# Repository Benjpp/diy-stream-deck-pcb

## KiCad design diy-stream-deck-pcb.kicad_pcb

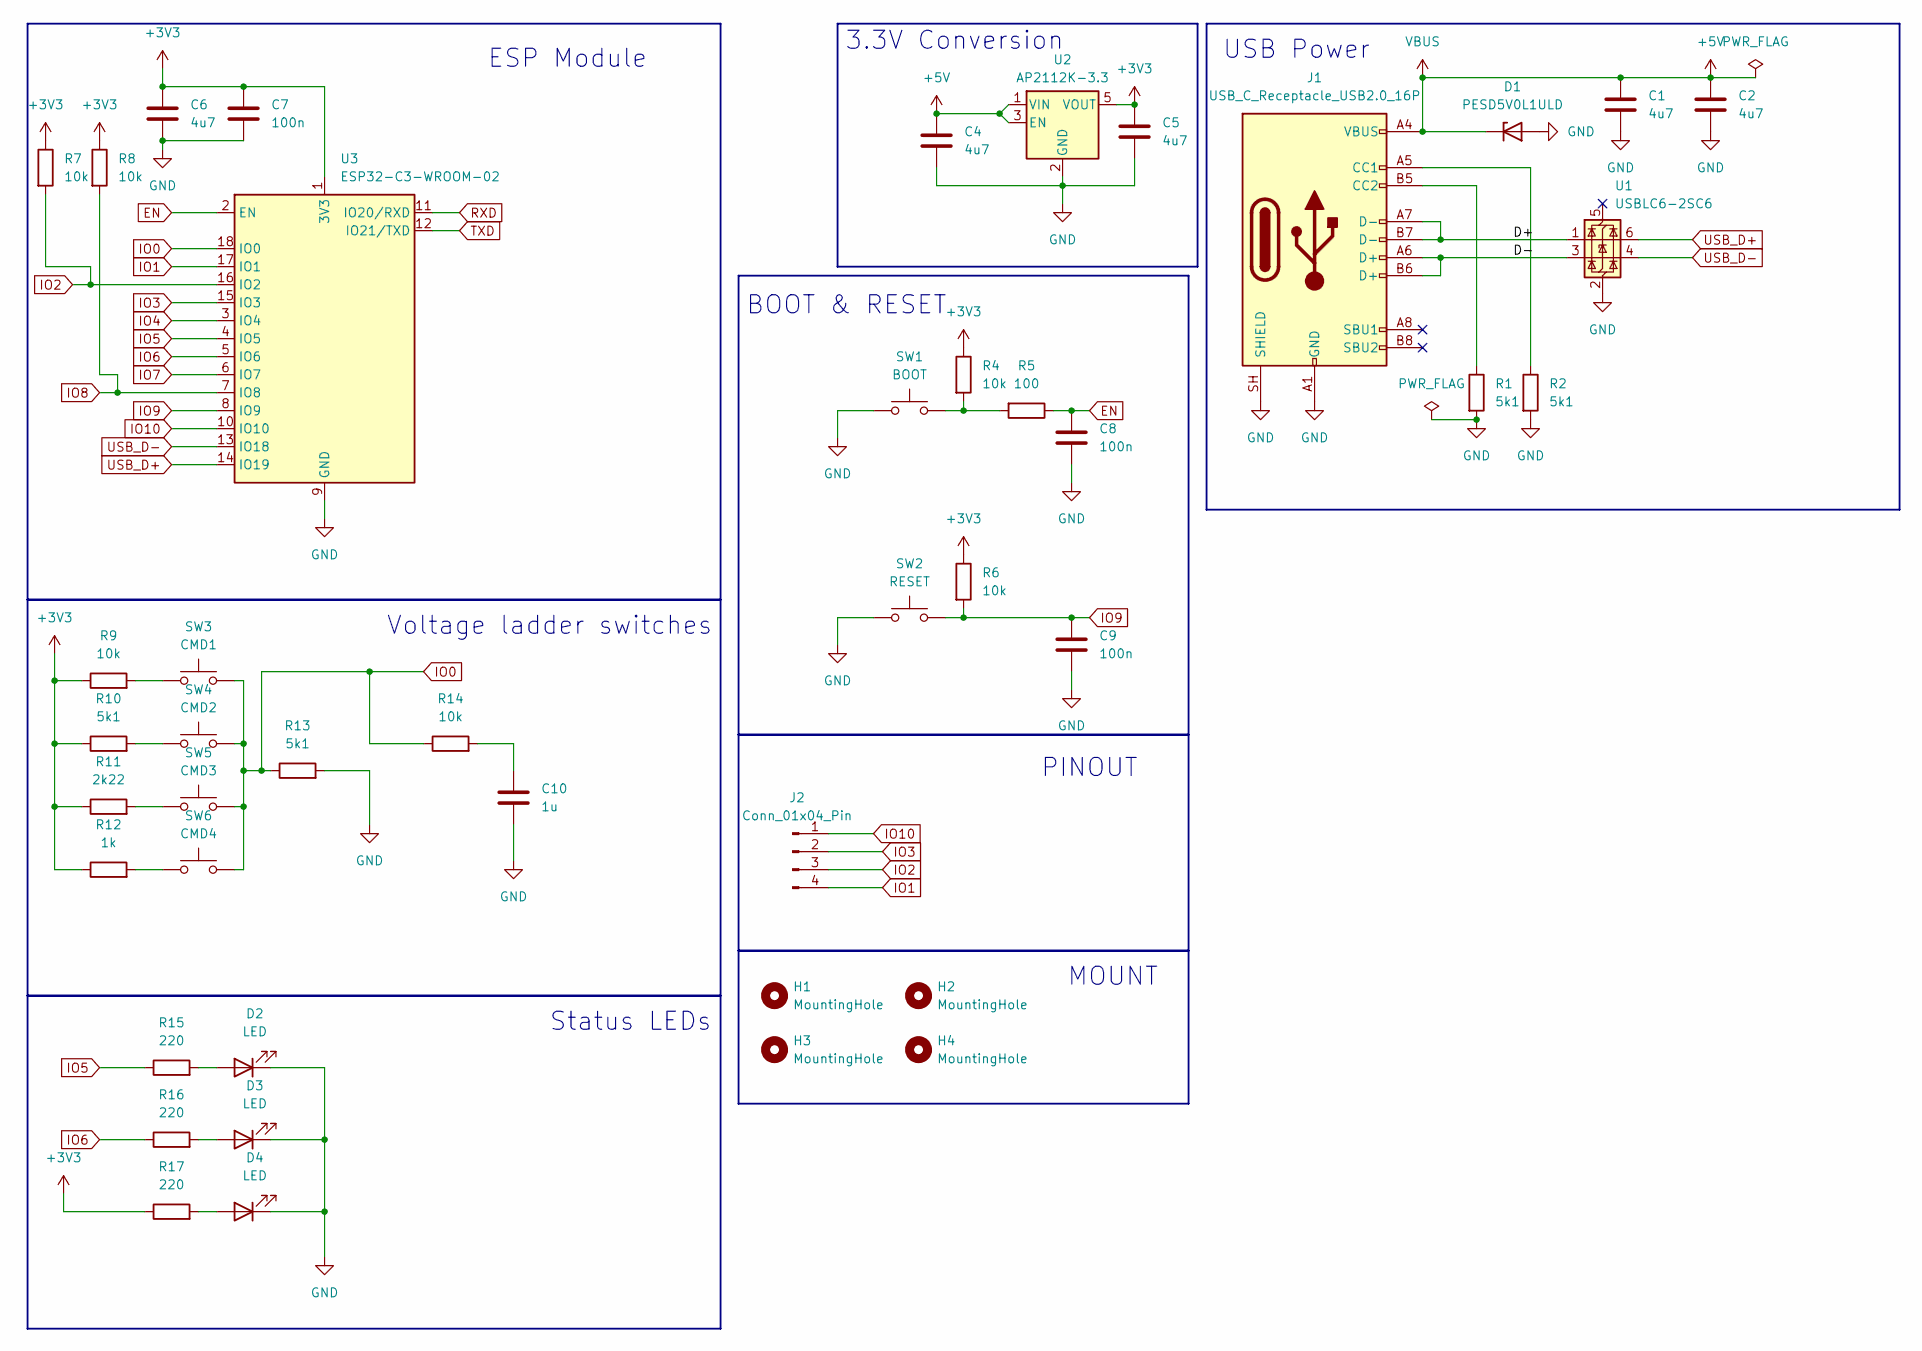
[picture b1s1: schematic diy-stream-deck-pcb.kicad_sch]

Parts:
C1, C2, C4, C5, C6: 4u7; C_0805_2012Metric
C7, C8, C9: 100n; C_0805_2012Metric
C10: 1u; C_Rect_L7.2mm_W5.0mm_P5.00mm
D1: PESD5V0L1ULD; D_SOD-882D
D2, D3, D4: LED; LED_D5.0mm
H1, H2, H3, H4: MountingHole; MountingHole_2.2mm_M2
J1: USB_C_Receptacle_USB2.0_16P; USB_C_Receptacle_G-Switch_GT-USB-7025
J2: Conn_01x04_Pin; PinHeader_1x04_P2.54mm_Vertical
R1, R2: 5k1; R_01005_0402Metric
R4, R6, R7, R8: 10k; R_0805_2012Metric
R5: 100; R_0805_2012Metric
R9, R14: 10k; R_Axial_DIN0207_L6.3mm_D2.5mm_P10.16mm_Horizontal
R10, R13: 5k1; R_Axial_DIN0207_L6.3mm_D2.5mm_P10.16mm_Horizontal
R11: 2k22; R_Axial_DIN0207_L6.3mm_D2.5mm_P10.16mm_Horizontal
R12: 1k; R_Axial_DIN0207_L6.3mm_D2.5mm_P10.16mm_Horizontal
R15, R16, R17: 220; R_Axial_DIN0207_L6.3mm_D2.5mm_P10.16mm_Horizontal
SW1: BOOT; SW_SPST_B3U-1000P
SW2: RESET; SW_SPST_B3U-1000P
SW3: CMD1; SW_SPST_B3U-1000P
SW4: CMD2; SW_SPST_B3U-1000P
SW5: CMD3; SW_SPST_B3U-1000P
SW6: CMD4; SW_SPST_B3U-1000P
U1: USBLC6-2SC6; SOT-23-6
U2: AP2112K-3.3; SOT-23-5
U3: ESP32-C3-WROOM-02

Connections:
+3V3: C5.1, C6.1, C7.1, R4.1, R6.1, R7.1, R8.1, R9.1, R10.1, R11.1, R12.1, R17.1, U2.5 (VOUT), U3.1 (3V3)
+5V: C1.1, C2.1, C4.1, D1.1 (K), J1.A4 (VBUS), J1.A9 (VBUS), J1.B4 (VBUS), J1.B9 (VBUS), U2.1 (VIN), U2.3 (EN)
/D+: J1.A7 (D-), J1.B7 (D-), U1.1 (I/O1)
/D-: J1.A6 (D+), J1.B6 (D+), U1.3 (I/O2)
EN: C8.1, R5.1, U3.2 (EN)
GND: C1.2, C2.2, C4.2, C5.2, C6.2, C7.2, C8.2, C9.2, C10.2, D1.2 (A), D2.1 (K), D3.1 (K), D4.1 (K), J1.A1 (GND), J1.A12 (GND), J1.B1 (GND), J1.B12 (GND), J1.SH (SHIELD), R1.2, R2.2, R13.2, SW1.1, SW2.1, U1.2 (GND), U2.2 (GND), U3.9 (GND), U3.19 (GND)
IO0: R13.1, R14.1, SW3.2, SW4.2, SW5.2, SW6.2, U3.18 (IO0)
IO1: J2.4, U3.17 (IO1)
IO2: J2.3, R7.2, U3.16 (IO2)
IO3: J2.2, U3.15 (IO3)
IO4: U3.3 (IO4)
IO5: R15.1, U3.4 (IO5)
IO6: R16.1, U3.5 (IO6)
IO7: U3.6 (IO7)
IO8: R8.2, U3.7 (IO8)
IO9: C9.1, R6.2, SW2.2, U3.8 (IO9)
IO10: J2.1, U3.10 (IO10)
unnamed: C10.1, R14.2
unnamed: D2.2 (A), R15.2
unnamed: D3.2 (A), R16.2
unnamed: D4.2 (A), R17.2
unnamed: J1.A5 (CC1), R2.1
unnamed: J1.B5 (CC2), R1.1
unnamed: R4.2, R5.2, SW1.2
unnamed: R9.2, SW3.1
unnamed: R10.2, SW4.1
unnamed: R11.2, SW5.1
unnamed: R12.2, SW6.1
RXD: U3.11 (IO20/RXD)
TXD: U3.12 (IO21/TXD)
USB_D+: U1.6 (I/O1), U3.14 (IO19)
USB_D-: U1.4 (I/O2), U3.13 (IO18)

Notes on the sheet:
BOOT & RESET
MOUNT
ESP Module
Status LEDs
3.3V Conversion
Voltage ladder switches
USB Power
PINOUT

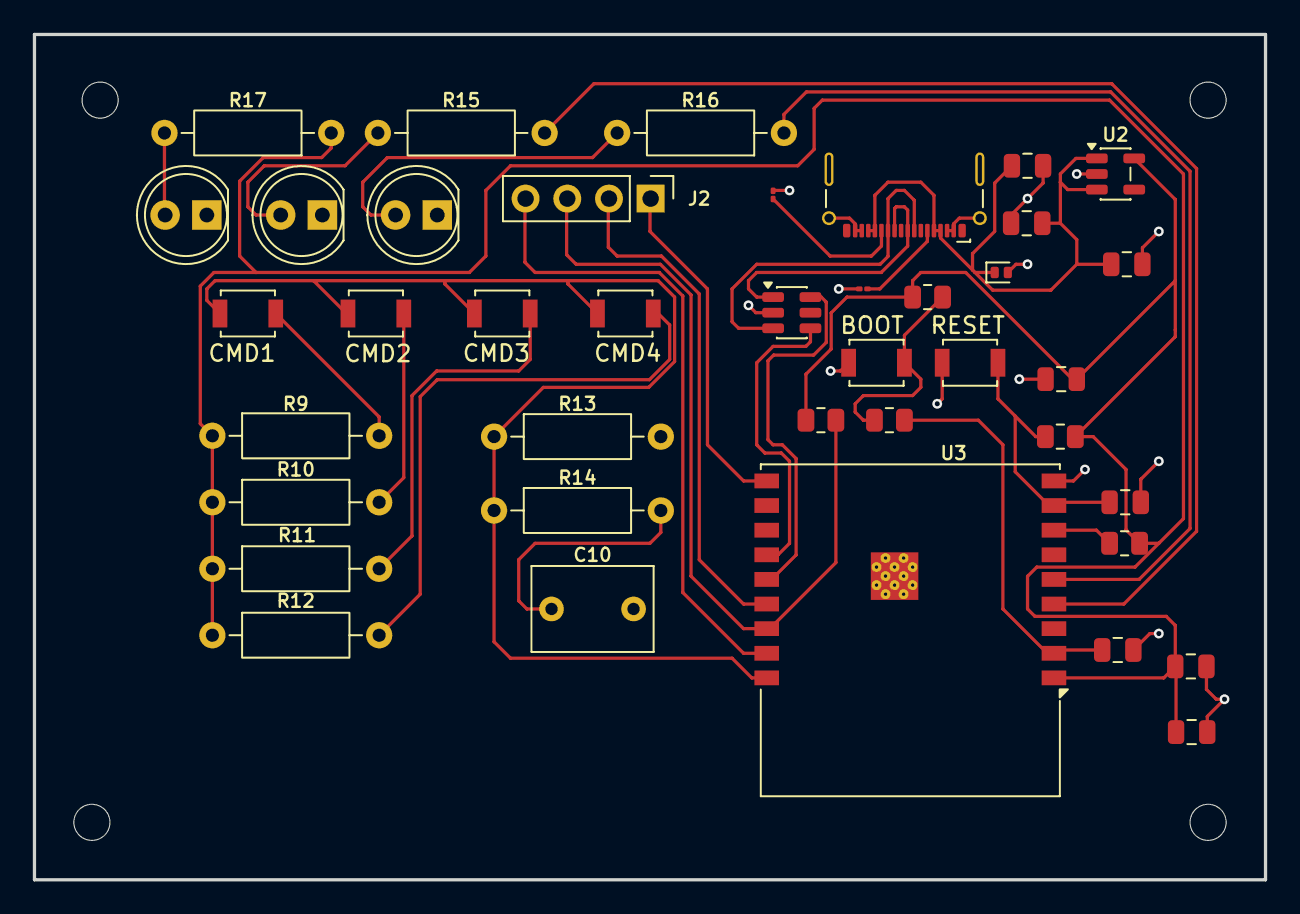
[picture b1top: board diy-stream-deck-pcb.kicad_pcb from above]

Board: 2 copper layers, 75.0 x 51.5 mm, 44 parts (0 on the bottom side), 28 nets.

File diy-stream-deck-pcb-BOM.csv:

"Id";"Identificador";"Huella";"Cantidad";"Identificación";"Suministrador y ref";
1;"C1, C2, C4, C5, C6";"C_0805_2012Metric";5;"4u7";;;
2;"C7, C8, C9";"C_0805_2012Metric";3;"100n";;;
3;"C10";"C_Rect_L7.2mm_W5.0mm_P5.00mm";1;"1u";;;
4;"D1";"D_SOD-882D";1;"PESD5V0L1ULD";;;
5;"D2, D3, D4";"LED_D5.0mm";3;"LED";;;
6;"J1";"USB_C_Receptacle_G-Switch_GT-USB-7025";1;"USB_C_Receptacle_USB2.0_16P";;;
7;"J2";"PinHeader_1x04_P2.54mm_Vertical";1;"Conn_01x04_Pin";;;
8;"R1, R2";"R_01005_0402Metric";2;"5k1";;;
9;"R3";"R_0805_2012Metric";1;"0";;;
10;"R4, R6, R7, R8";"R_0805_2012Metric";4;"10k";;;
11;"R5";"R_0805_2012Metric";1;"100";;;
12;"R9, R14";"R_Axial_DIN0207_L6.3mm_D2.5mm_P10.16mm_Horizontal";2;"10k";;;
13;"R10, R13";"R_Axial_DIN0207_L6.3mm_D2.5mm_P10.16mm_Horizontal";2;"5k1";;;
14;"R11";"R_Axial_DIN0207_L6.3mm_D2.5mm_P10.16mm_Horizontal";1;"2k22";;;
15;"R12";"R_Axial_DIN0207_L6.3mm_D2.5mm_P10.16mm_Horizontal";1;"1k";;;
16;"R15, R16, R17";"R_Axial_DIN0207_L6.3mm_D2.5mm_P10.16mm_Horizontal";3;"220";;;
17;"SW1";"SW_SPST_B3U-1000P";1;"BOOT";;;
18;"SW2";"SW_SPST_B3U-1000P";1;"RESET";;;
19;"SW3";"SW_SPST_B3U-1000P";1;"CMD1";;;
20;"SW4";"SW_SPST_B3U-1000P";1;"CMD2";;;
21;"SW5";"SW_SPST_B3U-1000P";1;"CMD3";;;
22;"SW6";"SW_SPST_B3U-1000P";1;"CMD4";;;
23;"U1";"SOT-23-6";1;"USBLC6-2SC6";;;
24;"U2";"SOT-23-5";1;"AP2112K-3.3";;;
25;"U3";"ESP32-C3-WROOM-02";1;"ESP32-C3-WROOM-02";;;
